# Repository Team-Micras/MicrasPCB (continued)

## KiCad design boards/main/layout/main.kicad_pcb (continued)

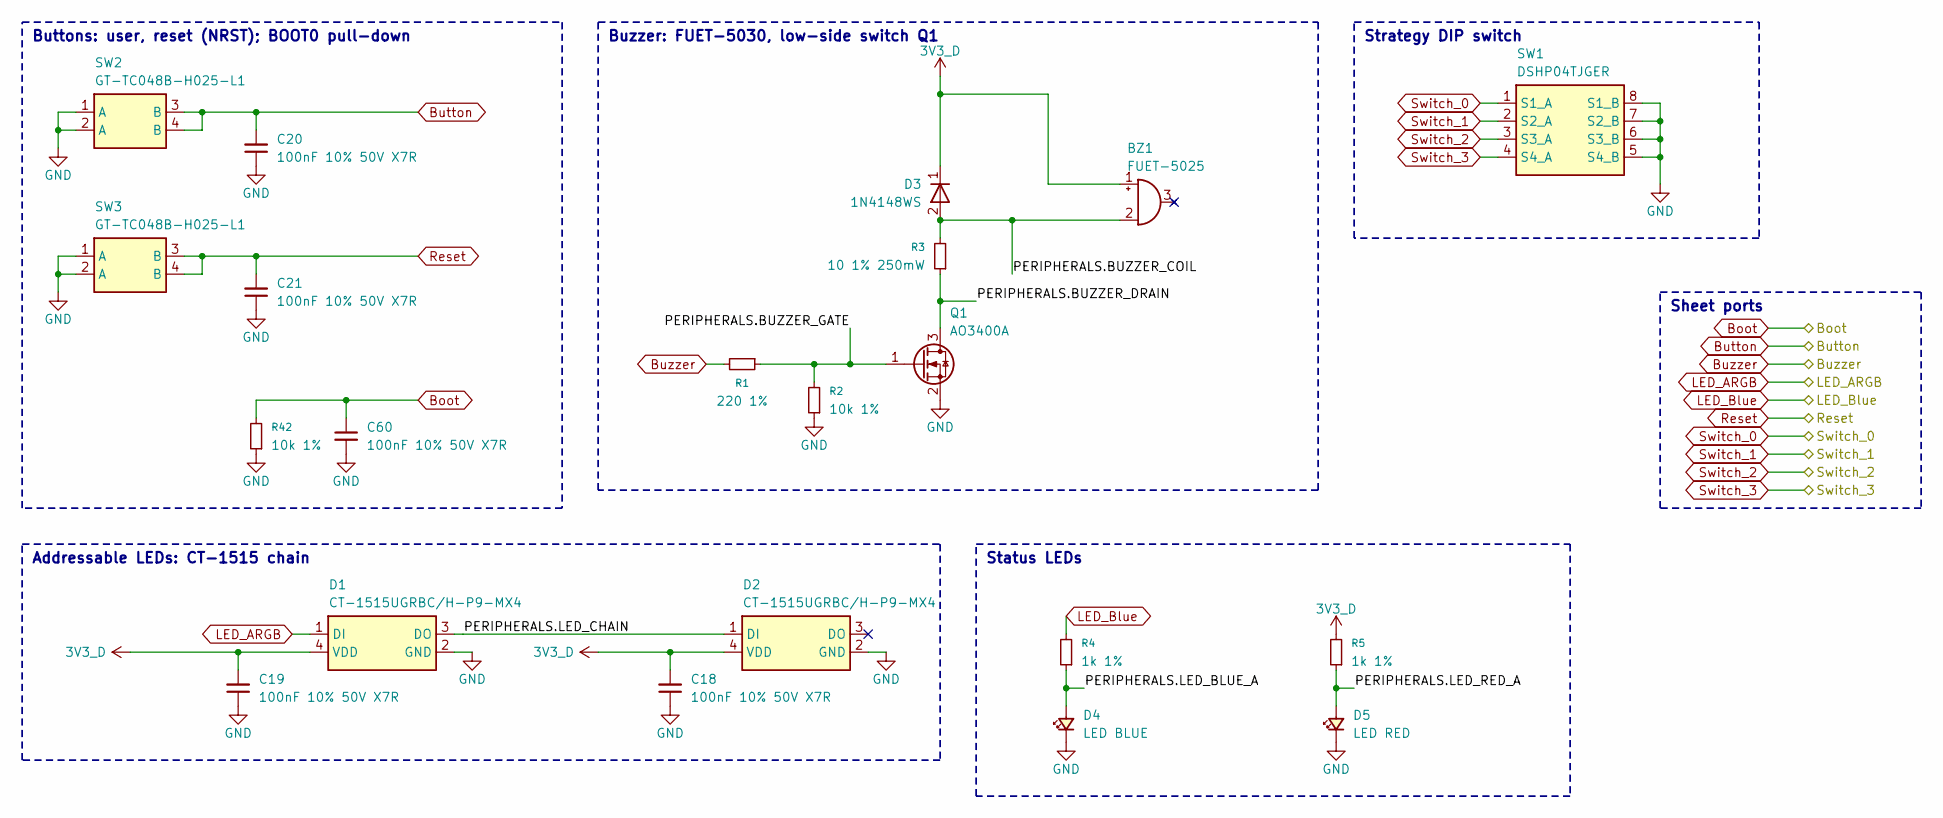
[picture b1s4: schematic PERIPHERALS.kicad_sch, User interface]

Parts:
BZ1: FUET-5025; BUZ-SMD_FST-5025
C18, C19, C20, C21, C60: 100nF 10% 50V X7R; C_0402_1005Metric
D1, D2: CT-1515UGRBC/H-P9-MX4; LED-SMD_4P-L1.5-W1.5-P1.04_CT-1515UGRBC
D3: 1N4148WS; D_SOD-323
D4: LED BLUE; LED_0603_1608Metric
D5: LED RED; LED_0603_1608Metric
Q1: AO3400A; SOT-23-3_L2.9-W1.3-P1.90-LS2.4-BR
R1: 220 1%; R_0402_1005Metric
R2, R42: 10k 1%; R_0402_1005Metric
R3: 10 1% 250mW; R_1206_3216Metric
R4, R5: 1k 1%; R_0402_1005Metric
SW1: DSHP04TJGER; SW-SMD_8P-L6.7-W5.4-P1.27-LS5.6
SW2, SW3: GT-TC048B-H025-L1; SW-SMD-4P_L4.2-W3.2_GT-TC048

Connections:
3V3_D: BZ1.1 (+), C18.2, C19.2, D1.4 (VDD), D2.4 (VDD), D3.1 (K), R5.2; also elsewhere on the board
Boot: C60.1, R42.2; also elsewhere on the board
Button: C20.2, SW2.3 (B), SW2.4 (B); also elsewhere on the board
Buzzer: R1.2; also elsewhere on the board
GND: C18.1, C19.1, C20.1, C21.1, C60.2, D1.2 (GND), D2.2 (GND), D4.1 (K), D5.1 (K), Q1.2 (S), R2.1, R42.1, SW1.5 (S4_B), SW1.6 (S3_B), SW1.7 (S2_B), SW1.8 (S1_B), SW2.1 (A), SW2.2 (A), SW3.1 (A), SW3.2 (A); also elsewhere on the board
LED_ARGB: D1.1 (DI); also elsewhere on the board
LED_Blue: R4.2; also elsewhere on the board
PERIPHERALS.BUZZER_COIL: BZ1.2 (-), D3.2 (A), R3.2
PERIPHERALS.BUZZER_DRAIN: Q1.3 (D), R3.1
PERIPHERALS.BUZZER_GATE: Q1.1 (G), R1.1, R2.2
PERIPHERALS.BZ1.NC_BUZZER_NC: BZ1.3 (NC)
PERIPHERALS.D2.NC_LED_DO: D2.3 (DO)
PERIPHERALS.LED_BLUE_A: D4.2 (A), R4.1
PERIPHERALS.LED_CHAIN: D1.3 (DO), D2.1 (DI)
PERIPHERALS.LED_RED_A: D5.2 (A), R5.1
Reset: C21.2, SW3.3 (B), SW3.4 (B); also elsewhere on the board
Switch_0: SW1.1 (S1_A); also elsewhere on the board
Switch_1: SW1.2 (S2_A); also elsewhere on the board
Switch_2: SW1.3 (S3_A); also elsewhere on the board
Switch_3: SW1.4 (S4_A); also elsewhere on the board

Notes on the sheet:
Buzzer: FUET-5030, low-side switch Q1
Buttons: user, reset (NRST); BOOT0 pull-down
Addressable LEDs: CT-1515 chain
Strategy DIP switch
Status LEDs
Sheet ports

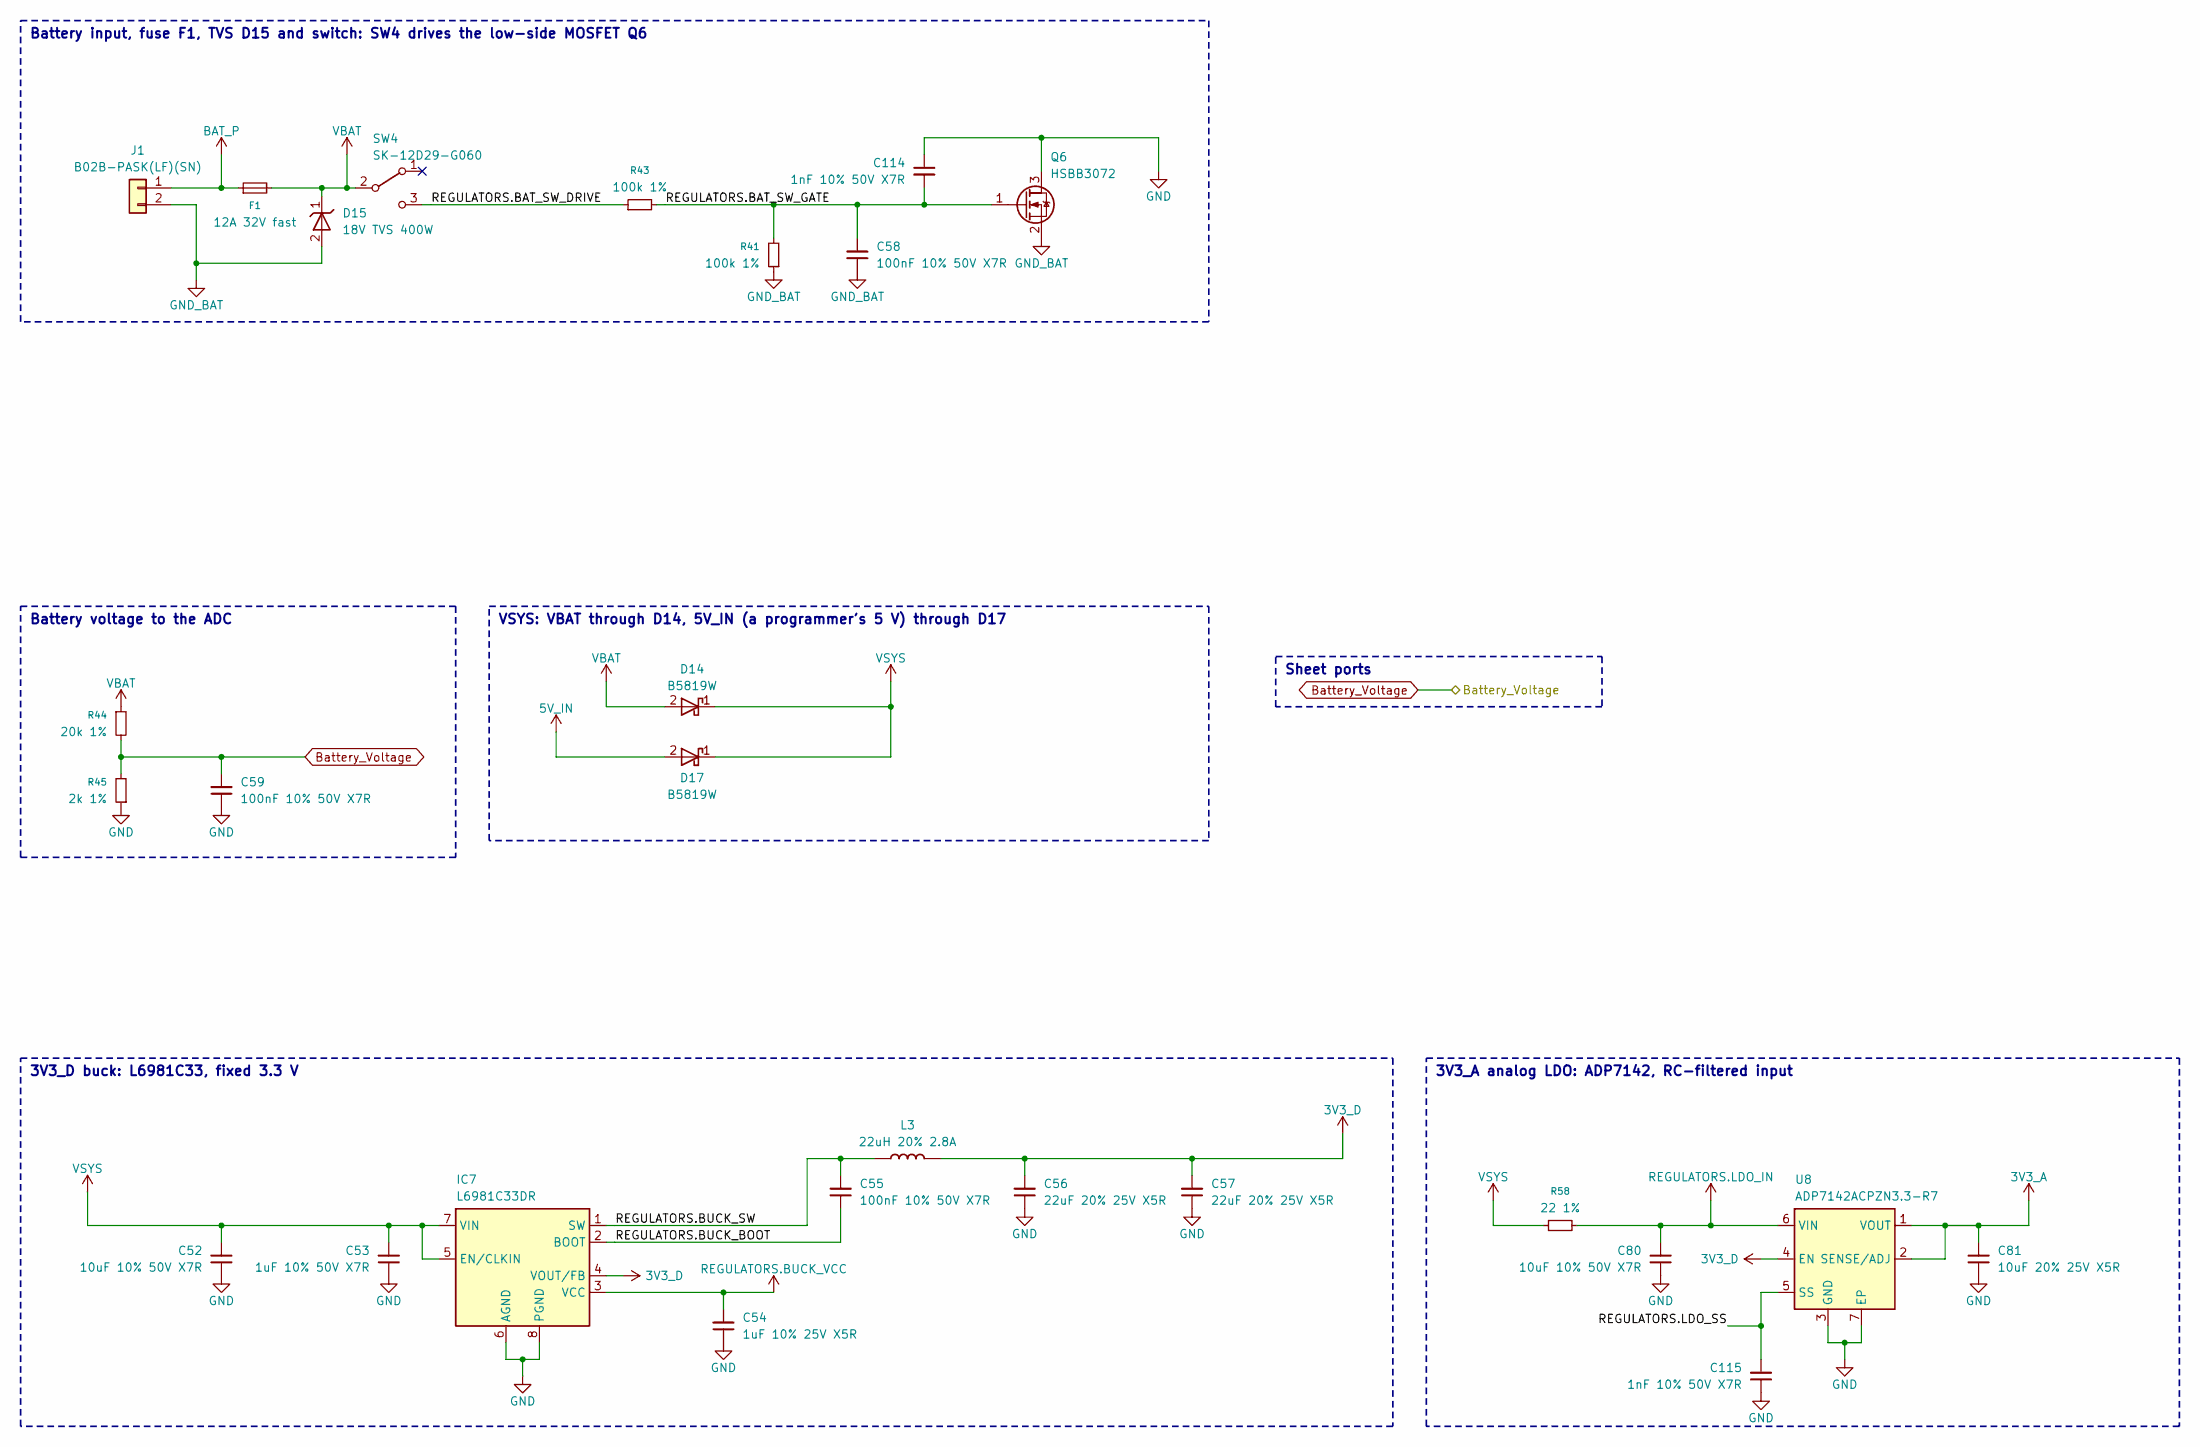
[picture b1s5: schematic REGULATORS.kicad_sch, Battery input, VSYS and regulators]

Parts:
C52, C80: 10uF 10% 50V X7R; C_1210_3225Metric
C53: 1uF 10% 50V X7R; C_0805_2012Metric
C54: 1uF 10% 25V X5R; C_0402_1005Metric
C55, C58, C59: 100nF 10% 50V X7R; C_0402_1005Metric
C56, C57: 22uF 20% 25V X5R; C_0805_2012Metric
C81: 10uF 20% 25V X5R; C_0603_1608Metric
C114, C115: 1nF 10% 50V X7R; C_0402_1005Metric
D14, D17: B5819W; D_SOD-123
D15: 18V TVS 400W; D_SMA
F1: 12A 32V fast; Fuse_Littelfuse_501_1206
IC7: L6981C33DR; SOIC127P600X175-8N
J1: B02B-PASK(LF)(SN); JST_PA_B02B-PASK_1x02_P2.00mm_Vertical
L3: 22uH 20% 2.8A; IND-SMD_L6.5-W6.0
Q6: HSBB3072; PRPAK-8_L3.0-W3.0-P0.65-BL-EP_SplitPaste
R41, R43: 100k 1%; R_0402_1005Metric
R44: 20k 1%; R_0402_1005Metric
R45: 2k 1%; R_0402_1005Metric
R58: 22 1%; R_0402_1005Metric
SW4: SK-12D29-G060; SW-TH_SK-12D29-G060
U8: ADP7142ACPZN3.3-R7; LFCSP-6-1EP_2x2mm_P0.65mm_EP1x1.6mm

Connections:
3V3_A: C81.2, U8.1 (VOUT), U8.2 (SENSE/ADJ); also elsewhere on the board
3V3_D: C56.2, C57.2, IC7.4 (VOUT/FB), L3.2, U8.4 (EN); also elsewhere on the board
5V_IN: D17.2 (A); also elsewhere on the board
BAT_P: F1.1, J1.1
Battery_Voltage: C59.2, R44.2, R45.2; also elsewhere on the board
GND: C52.1, C53.1, C54.1, C56.1, C57.1, C59.1, C80.1, C81.1, C114.1, C115.1, IC7.6 (AGND), IC7.8 (PGND), Q6.3 (D), R45.1, U8.3 (GND), U8.7 (EP); also elsewhere on the board
GND_BAT: C58.1, D15.2 (A), J1.2, Q6.2 (S), R41.1
REGULATORS.BAT_SW_DRIVE: R43.1, SW4.3 (B)
REGULATORS.BAT_SW_GATE: C58.2, C114.2, Q6.1 (G), R41.2, R43.2
REGULATORS.BUCK_BOOT: C55.1, IC7.2 (BOOT)
REGULATORS.BUCK_SW: C55.2, IC7.1 (SW), L3.1
REGULATORS.BUCK_VCC: C54.2, IC7.3 (VCC)
REGULATORS.LDO_IN: C80.2, R58.2, U8.6 (VIN)
REGULATORS.LDO_SS: C115.2, U8.5 (SS)
REGULATORS.SW4.NC_SK-12D29-G060_A: SW4.1 (A)
VBAT: D14.2 (A), D15.1 (K), F1.2, R44.1, SW4.2 (COM); also elsewhere on the board
VSYS: C52.2, C53.2, D14.1 (K), D17.1 (K), IC7.5 (EN/CLKIN), IC7.7 (VIN), R58.1

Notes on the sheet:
Battery input, fuse F1, TVS D15 and switch: SW4 drives the low-side MOSFET Q6
Battery voltage to the ADC
VSYS: VBAT through D14, 5V_IN (a programmer's 5 V) through D17
3V3_D buck: L6981C33, fixed 3.3 V
3V3_A analog LDO: ADP7142, RC-filtered input
Sheet ports

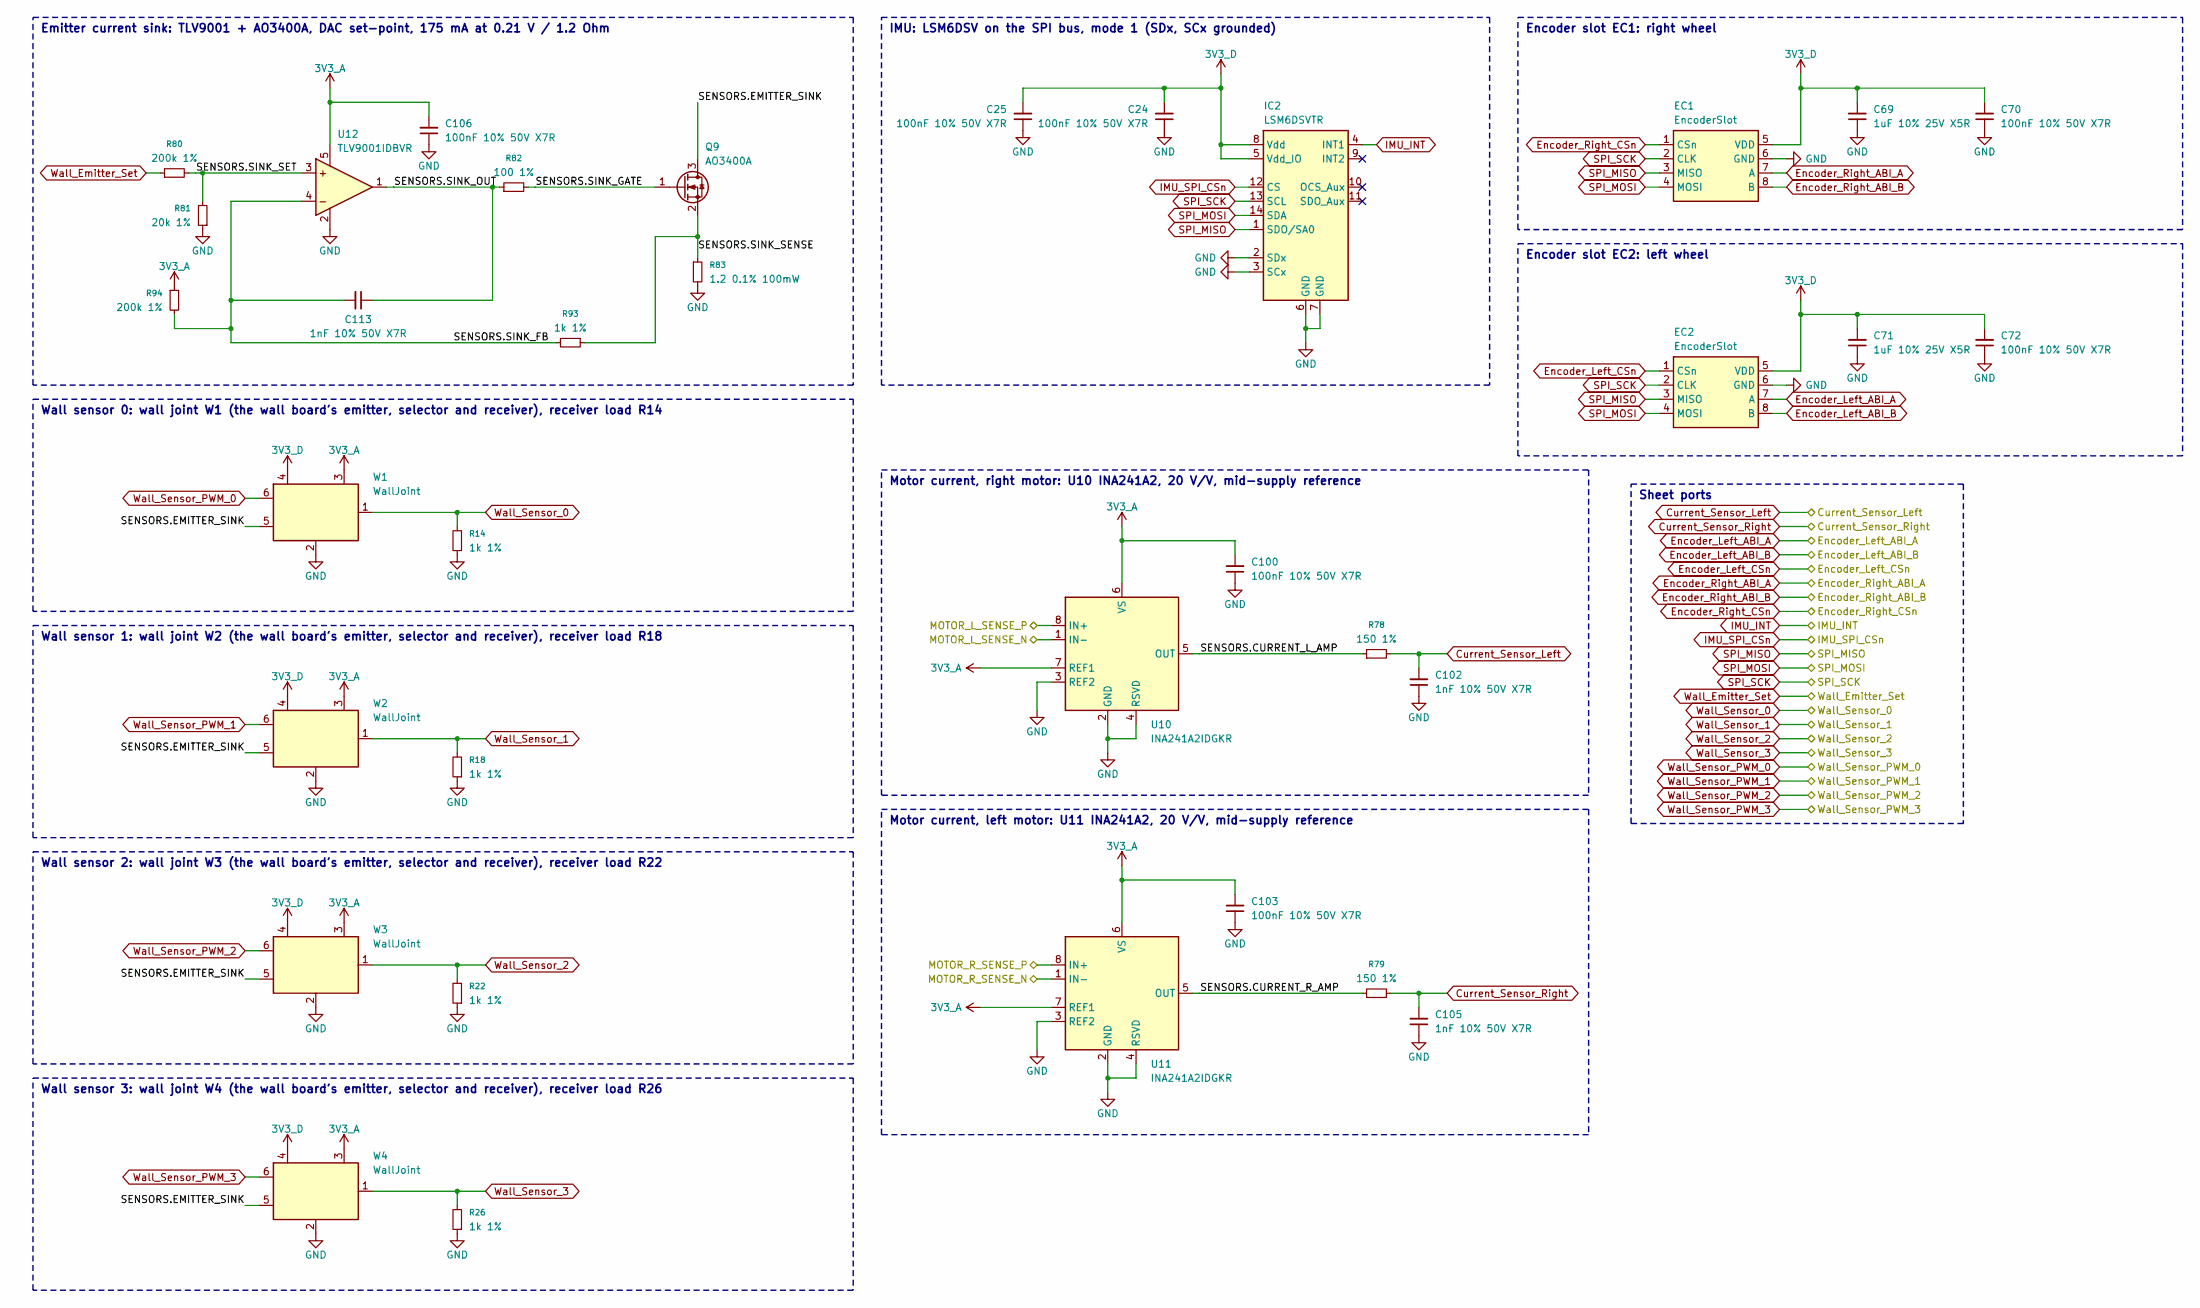
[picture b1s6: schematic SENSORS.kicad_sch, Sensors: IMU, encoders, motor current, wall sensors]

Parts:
C24, C25, C70, C72, C100, C103, C106: 100nF 10% 50V X7R; C_0402_1005Metric
C69, C71: 1uF 10% 25V X5R; C_0402_1005Metric
C102, C105, C113: 1nF 10% 50V X7R; C_0402_1005Metric
EC1, EC2: EncoderSlot; EncoderSlot_2x4_P0.95mm
IC2: LSM6DSVTR; LGA-14_3x2.5mm_P0.5mm
Q9: AO3400A; SOT-23-3_L2.9-W1.3-P1.90-LS2.4-BR
R14, R18, R22, R26, R93: 1k 1%; R_0402_1005Metric
R78, R79: 150 1%; R_0402_1005Metric
R80, R94: 200k 1%; R_0402_1005Metric
R81: 20k 1%; R_0402_1005Metric
R82: 100 1%; R_0402_1005Metric
R83: 1.2 0.1% 100mW; R_0603_1608Metric
U10, U11: INA241A2IDGKR; Texas_DGK0008A_VSSOP-8_3x3mm_P0.65mm
U12: TLV9001IDBVR; SOT-23-5
W1, W2, W3, W4: WallJoint; WallJoint_2x03_P1.27mm

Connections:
3V3_A: C100.2, C103.2, C106.2, R94.1, U10.6 (VS), U10.7 (REF1), U11.6 (VS), U11.7 (REF1), U12.5 (V+), W1.3 (3V3_A), W2.3 (3V3_A), W3.3 (3V3_A), W4.3 (3V3_A); also elsewhere on the board
3V3_D: C24.2, C25.2, C69.2, C70.2, C71.2, C72.2, EC1.5 (VDD), EC2.5 (VDD), IC2.5 (Vdd_IO), IC2.8 (Vdd), W1.4 (3V3_D), W2.4 (3V3_D), W3.4 (3V3_D), W4.4 (3V3_D); also elsewhere on the board
Current_Sensor_Left: C102.2, R78.2; also elsewhere on the board
Current_Sensor_Right: C105.2, R79.2; also elsewhere on the board
Encoder_Left_ABI_A: EC2.7 (A); also elsewhere on the board
Encoder_Left_ABI_B: EC2.8 (B); also elsewhere on the board
Encoder_Left_CSn: EC2.1 (CSn); also elsewhere on the board
Encoder_Right_ABI_A: EC1.7 (A); also elsewhere on the board
Encoder_Right_ABI_B: EC1.8 (B); also elsewhere on the board
Encoder_Right_CSn: EC1.1 (CSn); also elsewhere on the board
GND: C24.1, C25.1, C69.1, C70.1, C71.1, C72.1, C100.1, C102.1, C103.1, C105.1, C106.1, EC1.6 (GND), EC2.6 (GND), IC2.2 (SDx), IC2.3 (SCx), IC2.6 (GND), IC2.7 (GND), R14.1, R18.1, R22.1, R26.1, R81.1, R83.2, U10.2 (GND), U10.3 (REF2), U10.4 (RSVD), U11.2 (GND), U11.3 (REF2), U11.4 (RSVD), U12.2 (V-), W1.2 (GND), W2.2 (GND), W3.2 (GND), W4.2 (GND); also elsewhere on the board
IMU_INT: IC2.4 (INT1); also elsewhere on the board
IMU_SPI_CSn: IC2.12 (CS); also elsewhere on the board
Motor_L_Sense+: U10.8 (IN+); also elsewhere on the board
Motor_L_Sense-: U10.1 (IN-); also elsewhere on the board
Motor_R_Sense+: U11.8 (IN+); also elsewhere on the board
Motor_R_Sense-: U11.1 (IN-); also elsewhere on the board
SENSORS.CURRENT_L_AMP: R78.1, U10.5 (OUT)
SENSORS.CURRENT_R_AMP: R79.1, U11.5 (OUT)
SENSORS.EMITTER_SINK: Q9.3 (D), W1.5 (SINK), W2.5 (SINK), W3.5 (SINK), W4.5 (SINK)
SENSORS.IC2.NC_LSM6DSV_INT2: IC2.9 (INT2)
SENSORS.IC2.NC_LSM6DSV_OCS_Aux: IC2.10 (OCS_Aux)
SENSORS.IC2.NC_LSM6DSV_SDO_Aux: IC2.11 (SDO_Aux)
SENSORS.SINK_FB: C113.2, R93.2, R94.2, U12.4 (-)
SENSORS.SINK_GATE: Q9.1 (G), R82.2
SENSORS.SINK_OUT: C113.1, R82.1, U12.1 (OUT)
SENSORS.SINK_SENSE: Q9.2 (S), R83.1, R93.1
SENSORS.SINK_SET: R80.2, R81.2, U12.3 (+)
SPI_MISO: EC1.3 (MISO), EC2.3 (MISO), IC2.1 (SDO/SA0); also elsewhere on the board
SPI_MOSI: EC1.4 (MOSI), EC2.4 (MOSI), IC2.14 (SDA); also elsewhere on the board
SPI_SCK: EC1.2 (CLK), EC2.2 (CLK), IC2.13 (SCL); also elsewhere on the board
Wall_Emitter_Set: R80.1; also elsewhere on the board
Wall_Sensor_0: R14.2, W1.1 (OUT); also elsewhere on the board
Wall_Sensor_1: R18.2, W2.1 (OUT); also elsewhere on the board
Wall_Sensor_2: R22.2, W3.1 (OUT); also elsewhere on the board
Wall_Sensor_3: R26.2, W4.1 (OUT); also elsewhere on the board
Wall_Sensor_PWM_0: W1.6 (PWM); also elsewhere on the board
Wall_Sensor_PWM_1: W2.6 (PWM); also elsewhere on the board
Wall_Sensor_PWM_2: W3.6 (PWM); also elsewhere on the board
Wall_Sensor_PWM_3: W4.6 (PWM); also elsewhere on the board

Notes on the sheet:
Emitter current sink: TLV9001 + AO3400A, DAC set-point, 175 mA at 0.21 V / 1.2 Ohm
Wall sensor 0: wall joint W1 (the wall board's emitter, selector and receiver), receiver load R14
Wall sensor 1: wall joint W2 (the wall board's emitter, selector and receiver), receiver load R18
Wall sensor 2: wall joint W3 (the wall board's emitter, selector and receiver), receiver load R22
Wall sensor 3: wall joint W4 (the wall board's emitter, selector and receiver), receiver load R26
IMU: LSM6DSV on the SPI bus, mode 1 (SDx, SCx grounded)
Encoder slot EC1: right wheel
Encoder slot EC2: left wheel
Motor current, right motor: U10 INA241A2, 20 V/V, mid-supply reference
Motor current, left motor: U11 INA241A2, 20 V/V, mid-supply reference
Sheet ports

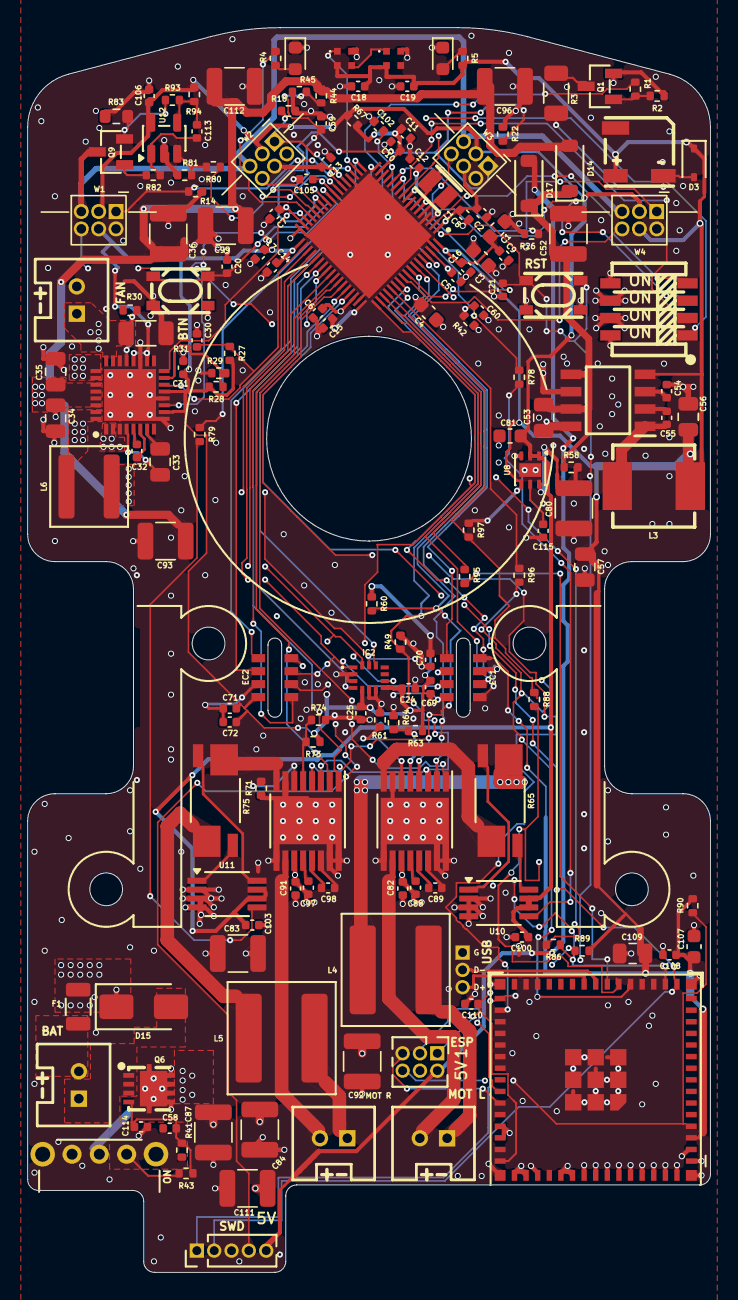
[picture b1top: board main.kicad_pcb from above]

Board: 4 copper layers, 50.0 x 91.1 mm, 168 parts (0 on the bottom side), 121 nets.

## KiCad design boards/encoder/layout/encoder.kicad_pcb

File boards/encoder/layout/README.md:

# Encoder board

One per wheel. An AS5047U magnetic angle sensor on a 9.6 x 14.1 mm, 2-layer, 0.79 mm board that
stands upright in a slot in the main board, facing the diametric magnet on the wheel axle. Supply
(3.3 V), SPI and the ABI quadrature outputs leave through the 8 edge pads of its tab, soldered to
the main board beside the slot.

The board is the MicrasEncoder Altium design (`hw_debug/modules/encoder`): its designators,
footprints, net names, outline, pours, sensor and tab placement, SPI and ABI routing and
silkscreen, plus three pull resistors the AS5047U asks for on its SPI inputs (R1-R3, see
[Circuit](#circuit)). `micras-pcb previous compare encoder` checks the netlist against that
design's connectivity ([`previous/board.json`](../previous/board.json)) with the change declared in
[`changes.toml`](../changes.toml).

## Files

The board files are in `boards/encoder/` (this README sits in its `layout/` folder);
`spec/` is at the repository root.

| File | Contents |
|---|---|
| [`encoder.zen`](../encoder.zen) | IC1 (AS5047U), C1, R1-R3, the edge tab J1, net names, stackup and rules |
| [`schematic/`](../schematic) | how the sheet is drawn (`micras-pcb sch`): the tab wired to the sensor, the SPI pulls |
| [`test/`](../test) | `pcb test` bench of the board's circuit: one 3V3 supply from the tab, the 100 nF at the sensor, the SPI input pulls, capacitor ratings |
| [`changes.toml`](../changes.toml) | the connectivity this board adds to the previous revision's (R1-R3) |
| [`layout/`](.) | this folder: the KiCad project; the `.kicad_pcb` holds placement and routing; [`fixes.py`](fixes.py) and [`fork.py`](fork.py) (the 3V3 fork at IC1 squared) are the scripts that turned the previous layout into this one |
| [`previous/`](../previous) | the previous revision's snapshot, and [`transfer_layout.py`](../previous/transfer_layout.py), which builds the previous layout from that revision |
| [`spec/encoder.toml`](../../../spec/encoder.toml) | mechanical interface: thickness, outline, tab, sensor and tab positions |

## Circuit

| Designator | Part | Package | Notes |
|---|---|---|---|
| IC1 | ams OSRAM AS5047U-HTSM ([`components/ams/AS5047U`](../../../components/ams/AS5047U)) | TSSOP-14, `SOP65P640X120-14N` | 3.3 V mode: VDD and VDD3V3 on 3V3, TEST on GND, U/V/W and I/PWM open (DS v1-00 Figure 4, Figure 11) |
| C1 | Yageo CC0603KRX7R9BB104, 100 nF 10 % 50 V X7R (LCSC C14663, JLCPCB basic) | 0603 (KiCad `C_0603_1608Metric`) | the 100 nF of DS Figure 11 on 3V3 |
| R1 | Uni-Royal 0402WGF1002TCE, 10 kOhm 1 % (LCSC C25744, JLCPCB basic) | 0402 (KiCad `R_0402_1005Metric`) | CSn pull-up to 3V3 (DS Figure 4 notes 1, 2) |
| R2 | Uni-Royal 0402WGF1003TCE, 100 kOhm 1 % (LCSC C25741, JLCPCB basic) | 0402 | CLK pull-down (DS Figure 4 notes 1, 3) |
| R3 | Uni-Royal 0402WGF1003TCE, 100 kOhm 1 % (LCSC C25741, JLCPCB basic) | 0402 | MOSI pull-down (DS Figure 4 notes 1, 3) |
| J1 | edge tab ([`components/micras/EncoderTab`](../../../components/micras/EncoderTab)) | `ENCODER_CONN`, copper on the board | not in the BOM |

| Net | IC1 | J1 |
|---|---|---|
| `Encoder_CSn` | 1 CSn (and R1 pad 2) | 1 (bottom) |
| `SPI_SCK` | 2 CLK (and R2 pad 1) | 2 (bottom) |
| `SPI_MISO` | 3 MISO | 3 (bottom) |
| `SPI_MOSI` | 4 MOSI (and R3 pad 1) | 4 (bottom) |
| `3V3` | 11 VDD, 12 VDD3V3 (and C1 pad 1, R1 pad 1) | 5 (top) |
| `GND` | 5 TEST, 13 GND (and C1 pad 2, R2 pad 2, R3 pad 2) | 6 (top) |
| `Encoder_ABI_A` | 7 A | 7 (top) |
| `Encoder_ABI_B` | 6 B | 8 (top) |

The Altium schematic names a Fenghua 0603B104K500NT for C1 (LCSC C30926, a JLCPCB extended part);
the Yageo part has the same value, tolerance, rating, dielectric and package and is a basic part.
The firmware reads the angle over SPI and the ABI outputs; the index (I/PWM) and U, V, W outputs
stay open.

A floating digital input is not allowed (DS Figure 4 note 1). CSn, CLK and MOSI are driven only by
the main board's MCU, whose pins are in analog mode, released, during and just after reset (RM0468
Rev 3 section 11.3.1 p511), so the board pulls them as notes 2 and 3 ask: R1 holds CSn high, the
sensor deselected; R2 and R3 hold CLK and MOSI low, CLK at its SPI mode 1 idle level (DS Figure 18).
The pulls sit on this board, with the part that needs them, so they hold with any host. SPI_SCK and
SPI_MOSI are shared by both encoder boards and the IMU, whose SCL and SDA inputs have no pull-up
by default (LSM6DSV DS13476 Rev 5 Table 22), so nothing on the bus fights the pull-downs; with both
boards fitted the two 100 kOhm pull-downs act in parallel, 50 kOhm, 66 uA while the MCU drives a
line high. R1's 10 kOhm loads the
MCU's chip-select pin with 0.33 mA while it is low. The bench `spi_inputs_held` checks the three
pulls and their range.

## Layout

The layout is the Altium MicrasEncoder.PcbDoc's, transferred by
[`previous/transfer_layout.py`](../previous/transfer_layout.py), with the 3V3 route, C1 and R1-R3
placed by [`layout/fixes.py`](fixes.py):

- IC1 sits on the tab centre line with its centre 9.0 mm above the shoulder (the main board's top
  surface), pin 1 top left seen from the chip side.
- SPI leaves IC1 pins 1-4 on the top, drops through four vias under the package and runs on the
  bottom (0.38 mm tracks) to the bottom tab pads; A and B run on the top (0.254 mm) to the top
  pads.
- 3V3 runs on the top (0.254 mm) straight up from its tab pad to IC1 pins 11 and 12, over the
  bottom-side Encoder_CSn track. C1 sits right of it below IC1, pad 1 on the track, 4.0 mm from
  pin 11 (pad centres), as close as the courtyards allow.
- R3 and R2 sit above the bottom-side SPI_MOSI and SPI_SCK tracks, between IC1 and the tab, each
  with a via onto its track; R1 sits right of the 3V3 track, below C1, with a via and a short
  bottom-side track to Encoder_CSn. The vias of R2 and R3 touch the lower edge of the
  bottom-side logo; like the four SPI vias under the logo, they are tented.
- GND pours on both layers, joined by six vias along the sides, with the Altium polygons' neck
  widths (copper narrower than 0.1 mm on the top, 0.4 mm on the bottom is not poured, which keeps
  the bottom pour out of the channels between the SPI tracks) and solid pad connections. The
  copper connections keep the previous teardrops as plain zones (priority 100 and up, above the
  pours), one per track end, filled with a 0.1 mm minimum width, JLCPCB's minimum copper feature.
- Silkscreen: the pin names above the tab on each side and the IC1, C1 and J1 designators, all
  0.5 mm high with a 0.125 mm stroke (the owner's choice), and the Micras logo on the bottom. R1-R3 carry their designators on F.Fab only:
  beside an 0402 on this board a 0.5 mm label cannot keep the 0.1 mm silkscreen clearance.
- IC1 and J1 are locked where `spec/encoder.toml` puts them. The drill and placement origin of
  the fab outputs is the Altium origin, the tab's bottom left corner.
- The Edge.Cuts outline is the Altium one without its duplicated vertex (a 1 nm line at the top
  right corner, which KiCad reads as a malformed outline).

The board's silkscreen text minimum is 0.5 mm high with a 0.125 mm stroke, the owner's choice
(the height in `encoder.zen`, the stroke in `rules/kicad-severities.toml`, both checked by DRC and
by `tests/test_encoder.py`); JLCPCB recommends 1.0 mm. Regenerate the layout from the previous revision with:

```sh
MICRAS_PREVIOUS=~/codes/hw_debug python3 boards/encoder/previous/transfer_layout.py
python3 boards/encoder/layout/fixes.py
python3 boards/encoder/layout/fork.py
make gen && make check
```

## Mechanics

[`spec/encoder.toml`](../../../spec/encoder.toml): origin at the tab centre on the shoulder line, u to
the right seen from the chip side, v up. The Edge.Cuts outline is layout geometry; `micras-pcb
mech encoder` checks its features (9.6 mm width, 13.1 mm top with 1 mm corner radii, 8.0 mm
shoulder, the tapers to 7.457 mm, the 5.0 x 1.0 mm tab with 0.1 mm reliefs) and exports the layout
outline to `build/encoder/encoder_mech.json`. The stackup is the PcbDoc's: 0.70 mm FR-4 core
(Dk 4.5) and 35 um copper; with Zener's fixed 10 um solder mask a side it is 0.79 mm (Altium's
12.7 um resist makes 0.7954 mm). It is ordered as JLCPCB's 0.8 mm 2-layer board, leaded HASL
finish, green solder mask and white silkscreen (the stackup in `encoder.zen`, the owner's choices: the
v1 main board was ordered with HASL and worked; green is JLCPCB's base price). Solder mask expansion 0.02 mm, the Altium rule.

## Differences from the Altium board

Apart from the fixes of the [layout](#layout) (the 3V3 route, C1 moved, R1-R3 with their tracks and
vias, one of the two SPI_MOSI teardrops at IC1 pad 4 removed, the IC1 and C1 designators moved, IC1's
courtyard on F.CrtYd), the board's copper, mask, paste, drills and outline match the Altium
MicrasEncoder's own Gerbers (its CAMtastic output) except:

| What | This board | Altium board | Why |
|---|---|---|---|
| Pour to board edge | 0.21 mm | 0.195 mm | `rules/jlcpcb.kicad_dru`: JLCPCB's 0.2 mm routed-edge clearance plus 10 um for the fill's arc approximation |
| C1 | KiCad `C_0603_1608Metric`: 0.90 x 0.95 mm pads; KiCad silkscreen and 3D model (0.8 mm wide) | 0.75 x 0.94 mm pads, Altium's pad box and model (0.9 mm wide) | the stdlib generic capacitor's footprint |
| Teardrop cusps | thinner than 0.1 mm left out (the 3V3 teardrop at (150.1, 102.1) is that thin all over and has no copper) | drawn to a point | JLCPCB's 0.1 mm minimum copper feature |
| Texts | KiCad stroke font | Altium fonts | same strings, sizes and positions |
| Solder mask thickness | 10 um a side | 12.7 um | Zener's stackup has no mask thickness setting |

The joint with the main board (`tests/test_joint.py`, `tests/test_layout.py`): the tab pads carry
the slot pads' signals (`components/micras/EncoderSlot`), face them pad for pad (0.95 mm pitch,
0.6 mm wide) and run from 0.8 mm into the slot to 1.2 mm above the main board's surface. J1's
pads carry paste openings on both sides, so assembly pre-tins the tab pads for that joint.

## Known faults

None: the encoder board passes every gate of `make check` (build, warnings, its test benches,
layout-check, ERC, LVS, previous, DRC, DFM, its pytests, parts).

Requirements without a check on this board, and why:

- The design review (`hw_debug/schematic_review.md` m19) asks for 1 uF + 100 nF at the main
  board's encoder slots, since the encoder board's 100 nF sits at the end of the joint: a main
  board item.

## Open items

- [ ] Check the IC1, C1 and R1-R3 placement rotations in JLCPCB's assembly preview, then set
      `rotation_verified = true` in `parts/jlc.toml` (correct `rotation` first if needed).
- [ ] MicrasHardware models the board as a 9.6 x 13.1 mm rectangle, 0.77 mm thick, with the
      5.0 x 4.4 mm package body turned 90 degrees from the board's (D 5.0 mm runs along v): point it
      at `build/encoder/encoder_mech.json` instead of copied numbers.

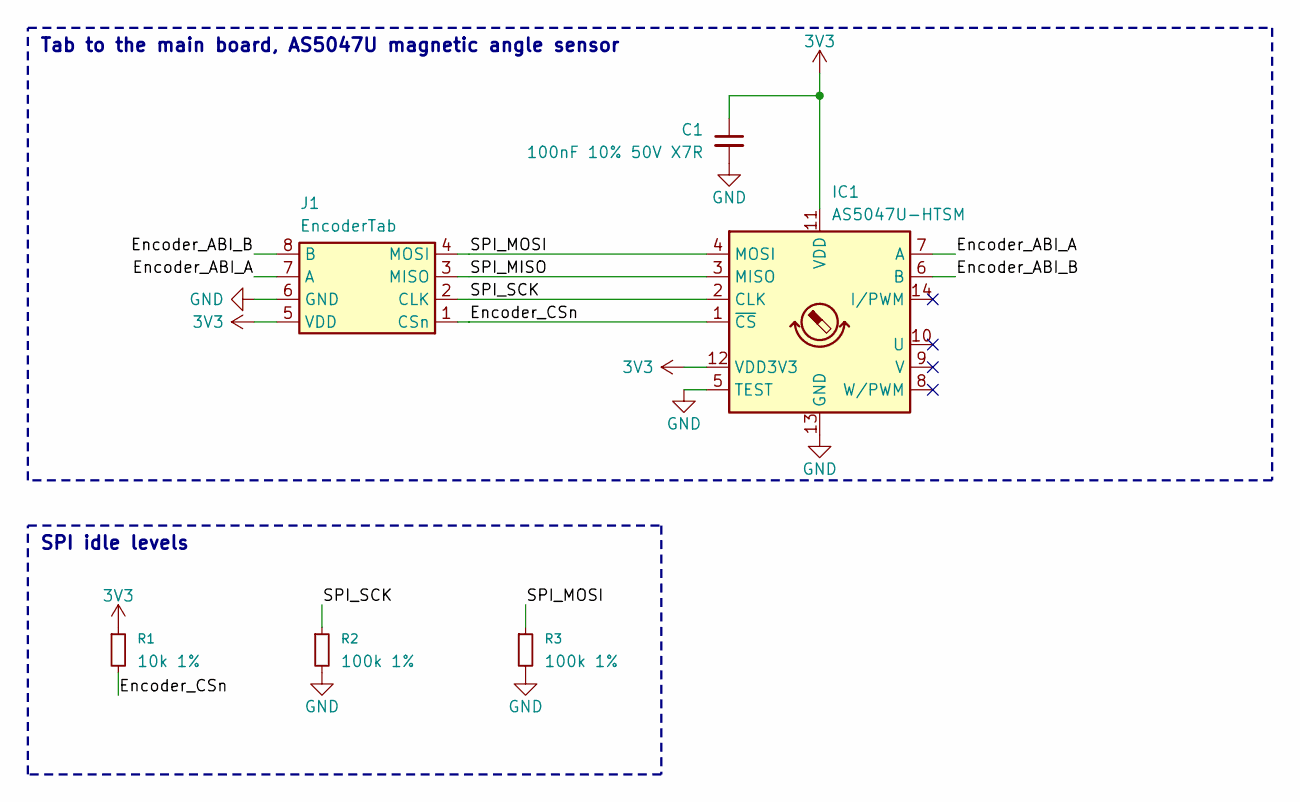
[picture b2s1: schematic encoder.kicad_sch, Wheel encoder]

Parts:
C1: 100nF 10% 50V X7R; C_0603_1608Metric
IC1: AS5047U-HTSM; SOP65P640X120-14N
J1: EncoderTab; ENCODER_CONN
R1: 10k 1%; R_0402_1005Metric
R2, R3: 100k 1%; R_0402_1005Metric

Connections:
3V3: C1.1, IC1.11 (VDD), IC1.12 (VDD3V3), J1.5 (VDD), R1.1
Encoder_ABI_A: IC1.7 (A), J1.7 (A)
Encoder_ABI_B: IC1.6 (B), J1.8 (B)
Encoder_CSn: IC1.1 (~CS), J1.1 (CSn), R1.2
GND: C1.2, IC1.5 (TEST), IC1.13 (GND), J1.6 (GND), R2.2, R3.2
IC1.NC_AS5047U_I/PWM: IC1.14 (I/PWM)
IC1.NC_AS5047U_U: IC1.10 (U)
IC1.NC_AS5047U_V: IC1.9 (V)
IC1.NC_AS5047U_W/PWM: IC1.8 (W/PWM)
SPI_MISO: IC1.3 (MISO), J1.3 (MISO)
SPI_MOSI: IC1.4 (MOSI), J1.4 (MOSI), R3.1
SPI_SCK: IC1.2 (CLK), J1.2 (CLK), R2.1

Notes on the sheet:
Tab to the main board, AS5047U magnetic angle sensor
SPI idle levels

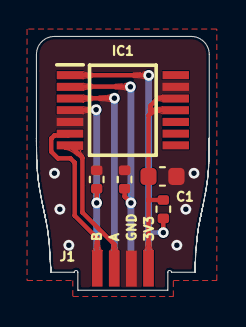
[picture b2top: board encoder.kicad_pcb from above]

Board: 2 copper layers, 9.6 x 14.1 mm, 6 parts (0 on the bottom side), 8 nets.

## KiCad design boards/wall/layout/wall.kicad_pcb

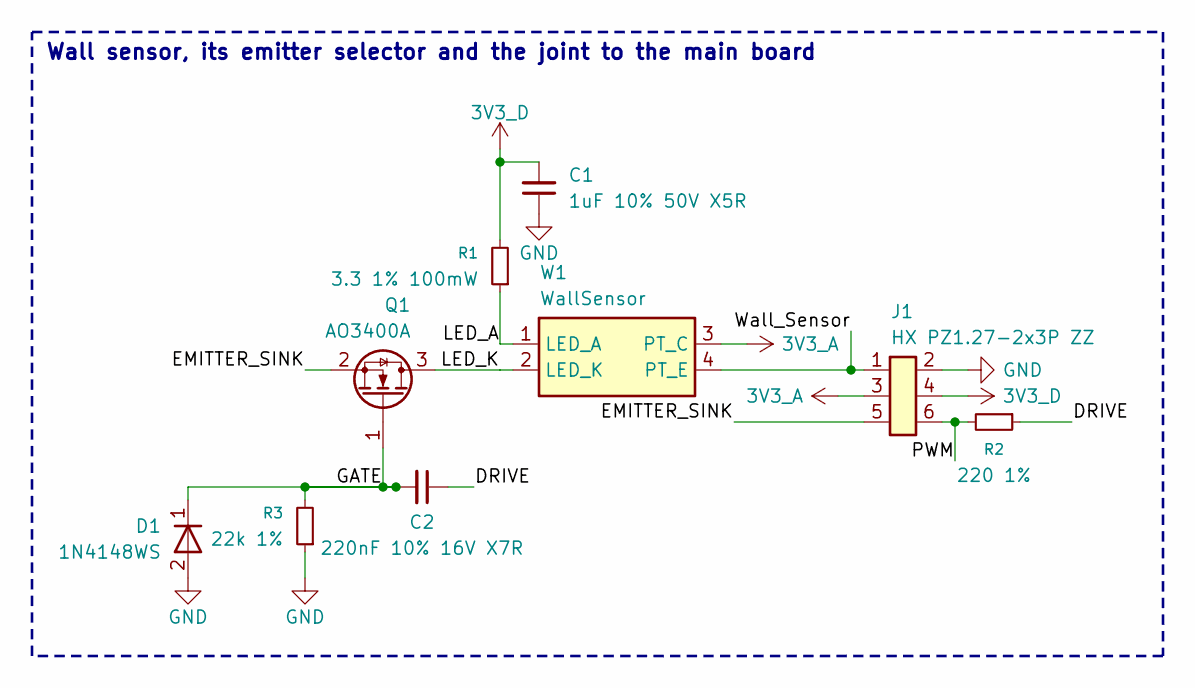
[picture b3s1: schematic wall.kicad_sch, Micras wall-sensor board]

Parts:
C1: 1uF 10% 50V X5R; C_0603_1608Metric
C2: 220nF 10% 16V X7R; C_0402_1005Metric
D1: 1N4148WS; D_SOD-323
J1: HX PZ1.27-2x3P ZZ; HX-PZ1.27-2x3P-ZZ_Straddle
Q1: AO3400A; SOT-23-3_L2.9-W1.3-P1.90-LS2.4-BR
R1: 3.3 1% 100mW; R_0603_1608Metric
R2: 220 1%; R_0402_1005Metric
R3: 22k 1%; R_0402_1005Metric
W1: WallSensor; WallSensor_SFH4550_TPS601A_Upright

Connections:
3V3_A: J1.3, W1.3 (PT_C)
3V3_D: C1.2, J1.4, R1.2
DRIVE: C2.1, R2.1
EMITTER_SINK: J1.5, Q1.2 (S)
GATE: C2.2, D1.1 (K), Q1.1 (G), R3.2
GND: C1.1, D1.2 (A), J1.2, R3.1
LED_A: R1.1, W1.1 (LED_A)
LED_K: Q1.3 (D), W1.2 (LED_K)
PWM: J1.6, R2.2
Wall_Sensor: J1.1, W1.4 (PT_E)

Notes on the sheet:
Wall sensor, its emitter selector and the joint to the main board

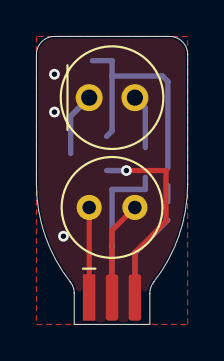
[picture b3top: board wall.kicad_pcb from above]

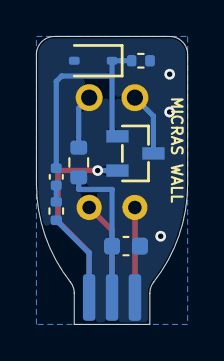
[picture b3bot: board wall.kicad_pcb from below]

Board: 2 copper layers, 8.4 x 16.0 mm, 9 parts (7 on the bottom side), 10 nets.
